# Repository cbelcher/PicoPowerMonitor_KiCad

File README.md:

# Pico Power Monitor KiCad Files

This the PCB project files, for the Pico Power Monitor.  I've included everything you need to open up this project in KiCad version 10.0.3 or newer.  Also included PCWay zip folder that you just need to drop on there site and checkout.  KiCad has the complete BOM needed to populate the project.

## Project is broken up into 4 sub-projects.

  - KiCad Custom PCB Design - This Repo.

	- PCBWay Shared Projects (Direct link [here](https://www.pcbway.com/project/shareproject/Pico_Power_Monitor_e0ff12c4.html))

  - PicoPowerMonitor - This is the Windows 11 application, completely optional.  The PicoPowerMonitor can and does run without this application.
  
	- Repo: /PicoPowerMonitor (Direct link [here](https://github.com/cbelcher/PicoPowerMonitor))
 
  - MicroPhython code to drive the hardware side of things.
		    
    - Repo: /RP2040PowerMonitor  (Direct link [here](https://github.com/cbelcher/RP2040PowerMonitor))
        This is the project that runs on the RP2040-Zero.  Current MicroPython firmware 1.28.
      
  - FreeCAD 3D Printed Case Design. (Direct link [here](https://github.com/cbelcher/PicoPowerMonitor_FreeCAD))

## CAD and Finished PCB Images

- Just unpacked PCB's from PCBWay.com

- 3D Render Shots of PCB from KiCad.

- Top with Through-hole Components

- Top with Through-hole & SMD Components

- Top No Compnents

- Bottom shot

- 1st unit off the projection line, getting put through its paces.
<p align="center">

## License

This project is licensed under the MIT License - see the [LICENSE](https://www.google.com/search?q=LICENSE) file for details.

## Acknowledgments

* KiCad.org for their amazing open-source CAD software.  [FreeCad.org](https://freecad.org))

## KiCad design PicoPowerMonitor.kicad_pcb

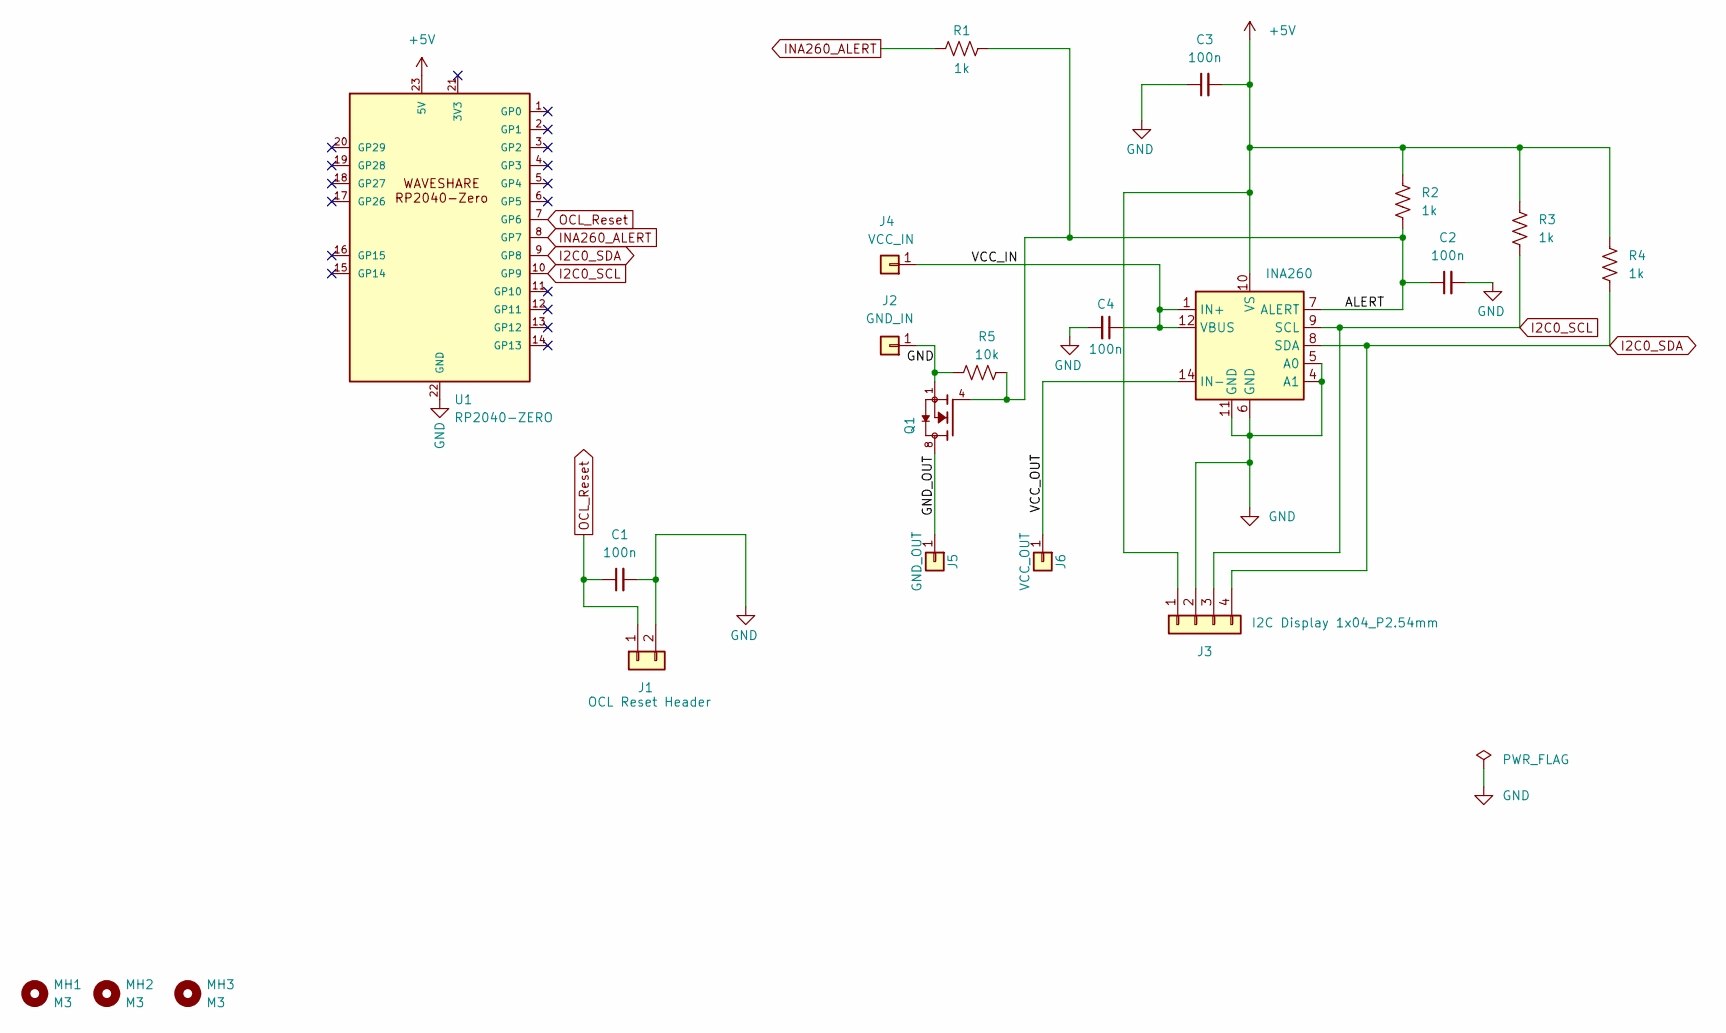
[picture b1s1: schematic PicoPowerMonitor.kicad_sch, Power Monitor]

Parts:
C1, C2, C3, C4: 100n; C_0603_1608Metric_Pad1.08x0.95mm_HandSolder
J1: OCL Reset Header; PinHeader_1x02_P2.54mm_Vertical
J2: GND_IN; 1_Banana_Jack_4mm_Panel_Cliff
J3: I2C Display 1x04_P2.54mm; PinHeader_1x04_P2.54mm_Vertical
J4: VCC_IN; 1_Banana_Jack_4mm_Panel_Cliff
J5: GND_OUT; 1_Banana_Jack_4mm_Panel_Cliff
J6: VCC_OUT; 1_Banana_Jack_4mm_Panel_Cliff
MH1, MH2, MH3: M3; MountingHole_3.2mm_M3
Q1: BSC007N04LS6ATMA1; TRANS_BSC007N04LS6ATMA1; DigiKey_Part_Number BSC007N04LS6ATMA1CT-ND
R1, R2, R3, R4: 1k; R_0603_1608Metric_Pad0.98x0.95mm_HandSolder
R5: 10k; R_0603_1608Metric_Pad0.98x0.95mm_HandSolder
U1: RP2040-ZERO; MODULE_RP2040-ZERO_Castellet_THT_SMD
U2: INA260; 1_INA260_TSSOP-16_4.4x5mm_P0.65mm

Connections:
+5V: C3.2, J3.1, R2.1, R3.1, R4.1, U1.23 (5V), U2.10 (VS)
/ALERT: C2.1, Q1.4, R1.2, R2.2, R5.1, U2.7 (ALERT)
/GND_OUT: J5.1 (Pin_1_1), Q1.8
/VCC_IN: C4.1, J4.1 (Pin_1_1), U2.1 (IN+), U2.12 (VBUS)
/VCC_OUT: J6.1 (Pin_1_1), U2.14 (IN-)
GND: C1.2, C2.2, C3.1, C4.2, J1.2, J2.1 (Pin_1_1), J3.2, Q1.1, R5.2, U1.22 (GND), U2.4 (A1), U2.5 (A0), U2.6 (GND), U2.11 (GND)
I2C0_SCL: J3.3, R3.2, U1.10 (GP9), U2.9 (SCL)
I2C0_SDA: J3.4, R4.2, U1.9 (GP8), U2.8 (SDA)
INA260_ALERT: R1.1, U1.8 (GP7)
OCL_Reset: C1.1, J1.1, U1.7 (GP6)

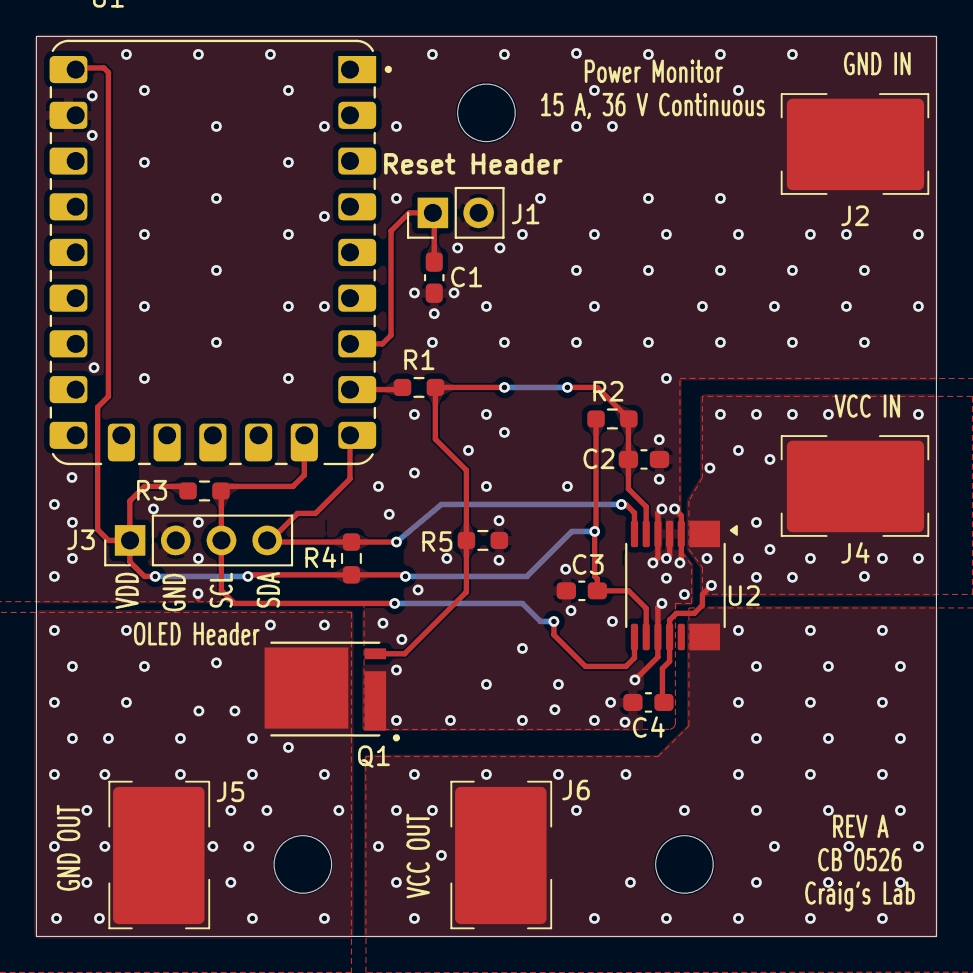
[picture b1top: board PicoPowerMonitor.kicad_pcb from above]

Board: 2 copper layers, 50.0 x 50.0 mm, 21 parts (0 on the bottom side), 10 nets.

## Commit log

2026-06-21 KiCad 10.0.3 production files
2026-06-21 Added PCBWay zip file. Everything you need to have to PCB created by PCBWay.
2026-06-21 First README commit
    This README includes project details for the Pico Power Monitor, including links to sub-projects, images of the PCB, and licensing information.
2026-06-21 Added new Image
    Added an image and description for the first unit off the projection line.
2026-06-21 Update README with PCBWay project link
    Added direct link to PCBWay shared projects in README.
2026-06-21 Nothing worth commenting on
2026-06-22 Fix links in README.md
    Corrected links in the README for RP2040PowerMonitor and FreeCAD case design.
2026-06-22 Fix formatting in README.md
